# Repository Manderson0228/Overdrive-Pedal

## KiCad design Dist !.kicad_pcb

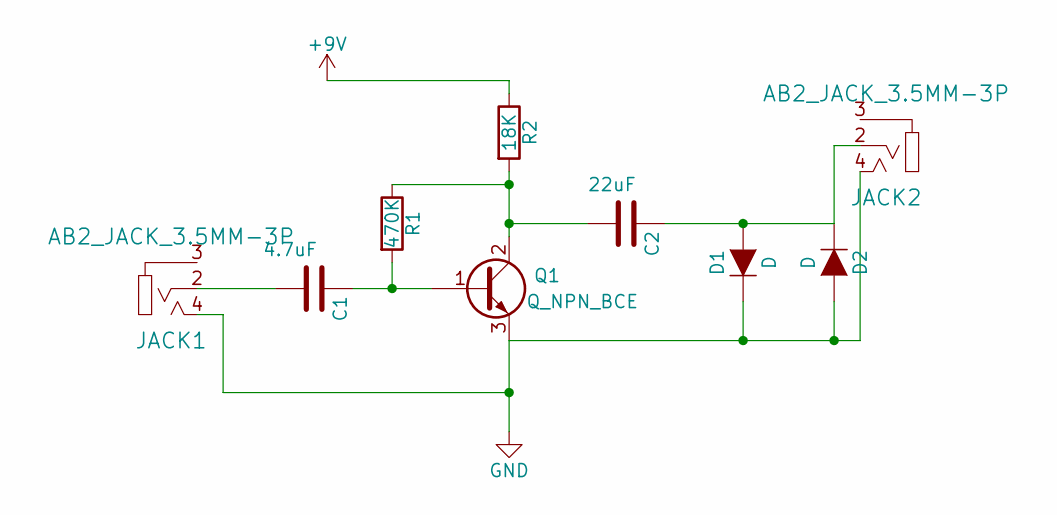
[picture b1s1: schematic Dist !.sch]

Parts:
C1: 4.7uF; C_Radial_D10_L20_P5
C2: 22uF; C_Radial_D10_L20_P5
D1, D2: D; Diode_DO-35_SOD27_Horizontal_RM10
JACK1, JACK2: AB2_JACK_3.5MM-3P; AB2_JACK_3.5MM-3P-PTH
Q1: Q_NPN_BCE; OldSowjetaera_Transistor_Type-II_SmallPads
R1: 470K; Resistor_Ceramic_Horizontal_L19mm-W8mm-H8mm-p25mm
R2: 18K; Resistor_Ceramic_Horizontal_L19mm-W8mm-H8mm-p25mm

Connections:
+9V: R2.1
GND: D1.1 (K), D2.2 (A), JACK1.4, JACK2.4, Q1.3 (E)
unnamed: C1.1, Q1.1 (B), R1.2
unnamed: C1.2, JACK1.2
unnamed: C2.1, D1.2 (A), D2.1 (K), JACK2.2
unnamed: C2.2, Q1.2 (C), R1.1, R2.2

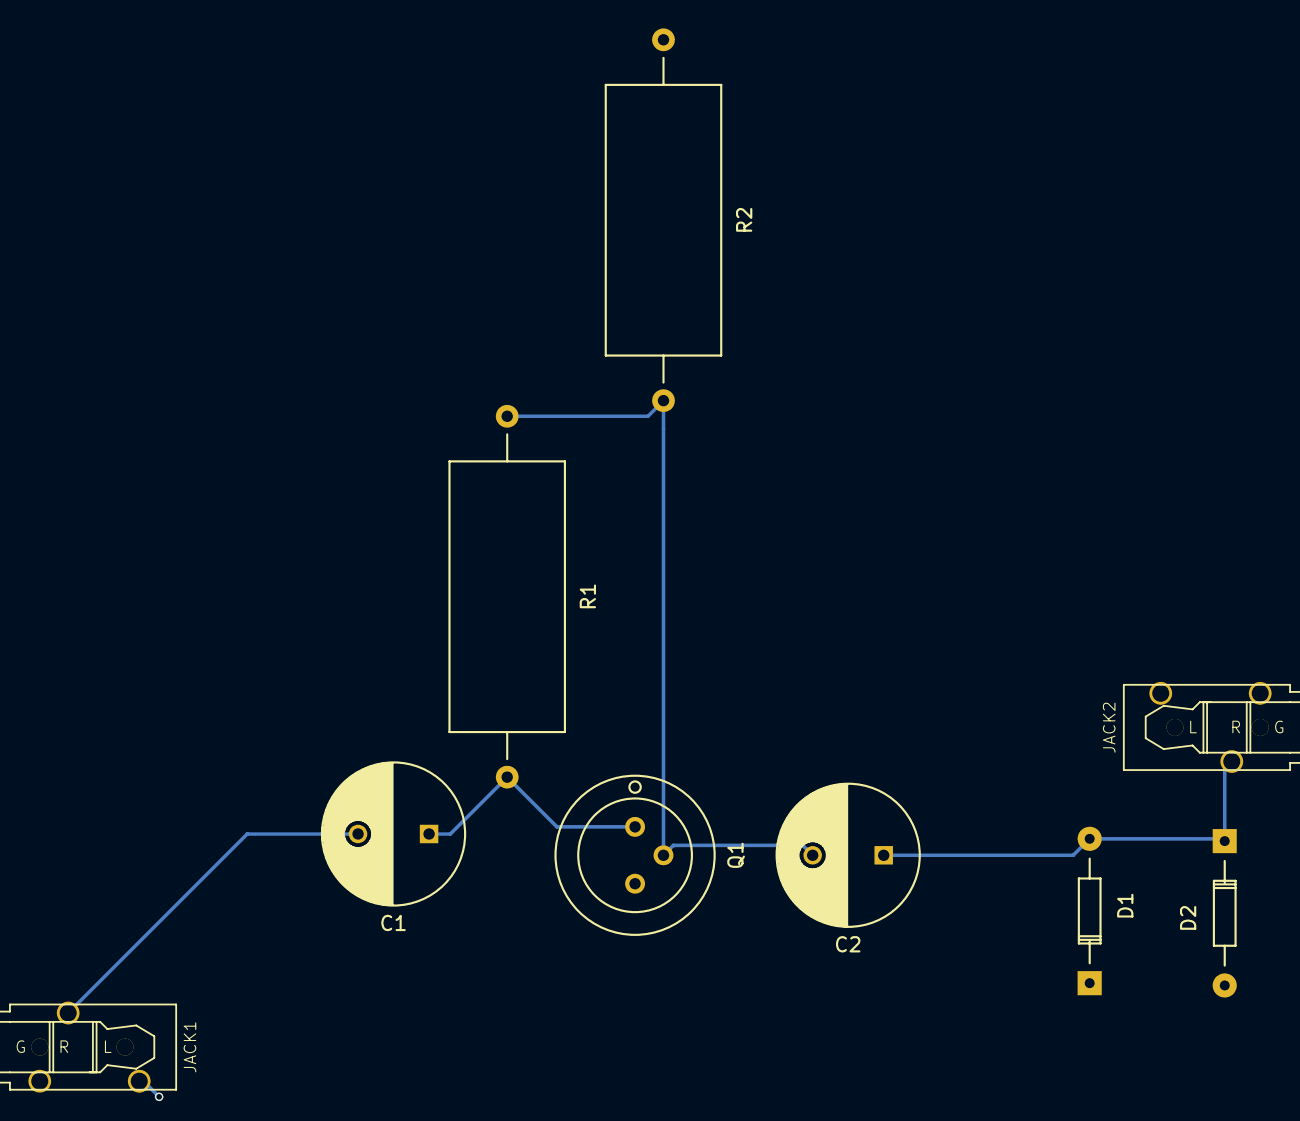
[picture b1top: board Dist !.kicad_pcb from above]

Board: 2 copper layers, 9 parts (0 on the bottom side), 5 nets.
